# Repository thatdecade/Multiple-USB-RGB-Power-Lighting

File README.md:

# Multiple USB RGB Power Lighting
The goal of this project is to set the color of two neopixel rings based on which USB cable is powered.  I plugged the USB cables into my game consoles, so when a console is powered, the shelf llght will have the corresponding color.

**How it Works**

Plug each USB cable into your separate devices.  The isolation diodes allow the trinket to be powered by any or all of the USB cables.  Periodically, the trinket will read the input pins to determine which USB cable is powered and will play the programmed animation and colors or combination of colors.

The trinket needs pull down resistors to set the idle state of an input pin when a USB cable is not powered or left unattached.

----

**Part List**

* Trinket 5V - <https://amzn.to/3gpQX6z>
* NeoPixel Ring - 16 RGB - <https://amzn.to/34wuUcn>
* Wired Under Cabinet Puck Lights - <https://amzn.to/2YssTdl>
* Backpack PCB - <https://oshpark.com/shared_projects/CATpwF4r>
* Three diodes - <https://octopart.com/search?q=CMF04%28TE12L%2CQ%2CM%29>
* Three 10k resistors - <https://octopart.com/search?q=RC0603FR-0710KL>
* Three USB Cables (dollar store)

The backpack pcb is optional.  You can just as easily wire up the diodes and resistors on a protoboard.  

**Pin Assignments**

Not all pins on the Trinket are equal.  Be sure to read Adafruit's help pages <https://learn.adafruit.com/introducing-trinket/pinouts>  Pins 3 and 4 should not be used as inputs and will conflict with talking to a PC for programming.

* GPIO #0 - Red Input, Attach to +5V wire from the first USB cable
* GPIO #1 - Blue Input, Attach to +5V wire from the second USB cable
* GPIO #2 - Green Input, Attach to +5V wire from the third USB cable
* GPIO #3 - Neopixel Data
* GPIO #4 - Potentiometer (optional)

I added a quick disconnect to Pin 4 so when I wanted to connect to the PC, I could remove the potentiometer without soldering.

**Assembly**

If you have access to a 3d printer, an enclosure stl is provided.  Thread the cables through the enclosure sides before soldering.

Solder the resistors and diodes to the backpack, then wire into the trinket.  Strip the USB cables and identify the 5V and Ground wires.  Use a multimeter to be sure, but the 5V and Ground wires can also be identified by thickness.  The power wires should be thicker than the data wires.

*There is a RGB LED and three 220 ohm resistors on the backback pcb for debugging, leave them unpopulated.*

Take apart the puck light and remove the PCB.  Recycling the wiring that came with the puck light to wire into your neopixel rings.  Use hot glue or epoxy to add the neopixel ring behind the puck light's diffuser.

**Programming**

Use the arduino ide and adafruit neopixel library and adafruit trinket board package.  Be sure to read Adafruit's help pages for each module.

* <https://learn.adafruit.com/adafruit-arduino-ide-setup/arduino-1-dot-6-x-ide>
* <https://learn.adafruit.com/introducing-trinket/setting-up-with-arduino-ide>
* <https://github.com/adafruit/Adafruit_NeoPixel>

If you followed my pin assignments, you can use the code without modification.  After you get the neopixels to light up and changing based on which USB cable is powered.   You can explore modifying the colors and animations.

**Usage, Testing, and Setting Colors**

After initial programming, when you plug in each of the three USB cables you should see the ring light up red or blue or green.  Combinations are allowed.

If you installed the optional potentiometer, you can change the color selected by a USB cable without reprogramming using a PC.  There are 16 colors preprogrammed to select from.

1. You will need two USB power ports to plug into.  
2. Connect the Micro USB on the trinket so power remains on while the other USBs are unplugged.  Leave this plugged in throughout these steps.
3. Take the USB cable you want to configure and plug it into your power block.  
4. Wait 5 seconds (or just wait for the animation to complete)
5. Rapidly unplug and plug the cable in four times, ending with the USB plugged in.
    1. You must complete this four times, before the spinning animation ends.
    2. If you do it right, the animations will stop and you will see a steady light.  
    3. If you mess up, wait 5 seconds before trying again.
6. Slowly rotate the potentiometer to select the color.
7. Unplug the USB cable to save the color selection.

----

**Additional Notes**

I used the NeoPixel ring and Trinket I listed above because that is what I had extra.  If I were to make one from scratch, I would use the [RGBW Neopixel Rings](https://octopart.com/search?q=adafruit+2854) and [Arduino NANO 33 IoT](https://amzn.to/3lg6Tfj) instead.  So I could use the Puck Light for normal lighting with commands to Alexa to change colors too!  

More Info: <https://blog.arduino.cc/2019/11/12/create-a-voice-controlled-device-with-alexa-and-arduino-iot-cloud-in-7-minutes/>

_We are a participant in the Amazon Services LLC Associates Program, an affiliate advertising program designed to provide a means for us to earn fees by linking to Amazon.com and affiliated sites._

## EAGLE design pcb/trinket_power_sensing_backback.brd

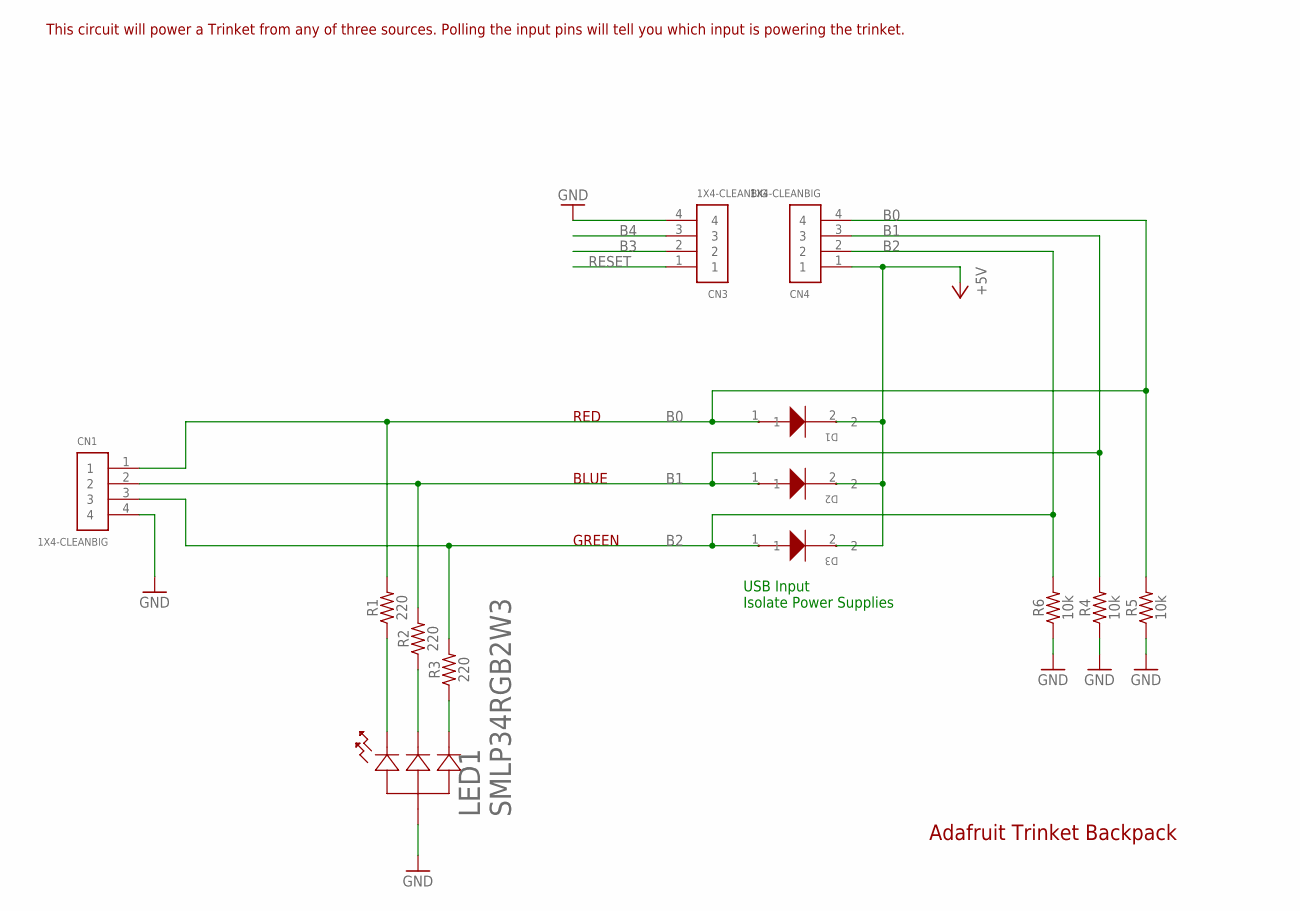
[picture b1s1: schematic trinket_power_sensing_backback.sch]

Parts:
CN1, CN3, CN4: 1X4-CLEANBIG; 1X04-CLEANBIG
D1, D2, D3: CMF04(TE12L,Q,M); M-FLAT_TOS
LED1: SMLP34RGB2W3; LED_SML-P24M_ROM
R1, R2, R3: 220; 0603
R4, R5, R6: 10k; 0603

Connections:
+5V: CN4.1, D1.2, D2.2, D3.2
B0: CN1.1, CN4.4, D1.1, R1.2, R5.2
B1: CN1.2, CN4.3, D2.1, R2.2, R4.2
B2: CN1.3, CN4.2, D3.1, R3.2, R6.2
B3: CN3.2
B4: CN3.3
GND: CN1.4, CN3.4, LED1.1, R4.1, R5.1, R6.1
unnamed: LED1.2, R1.1
unnamed: LED1.3, R2.1
unnamed: LED1.4, R3.1
RESET: CN3.1

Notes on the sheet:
Adafruit Trinket Backpack
USB Input Isolate Power Supplies
RED
BLUE
GREEN
This circuit will power a Trinket from any of three sources. Polling the input pins will tell you which input is powering the trinket.

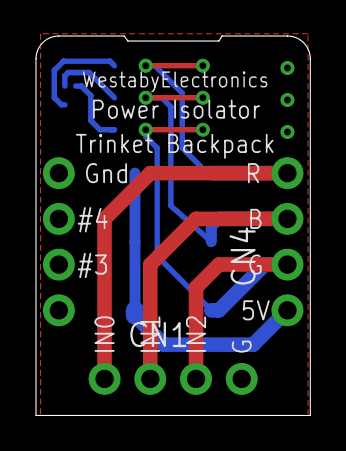
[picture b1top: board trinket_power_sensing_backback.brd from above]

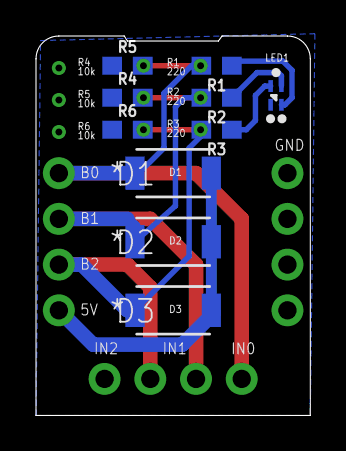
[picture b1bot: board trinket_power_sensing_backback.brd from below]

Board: 2 copper layers, 15.2 x 21.1 mm, 13 parts (10 on the bottom side), 8 nets.

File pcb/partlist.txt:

Partlist

EAGLE Version 7.7.0 Copyright (c) 1988-2016 CadSoft

Assembly variant: 

Part     Value            Package          Library            Position (inch)       Orientation

D1       CMF04(TE12L,Q,M) M-FLAT_TOS       CMF04(TE12L,Q)     (0.3 0.55)            MR0
D2       CMF04(TE12L,Q,M) M-FLAT_TOS       CMF04(TE12L,Q)     (0.3 0.4)             MR0
D3       CMF04(TE12L,Q,M) M-FLAT_TOS       CMF04(TE12L,Q)     (0.3 0.25)            MR0
LED1     SMLP34RGB2W3     LED_SML-P24M_ROM SMLP34RGB2W3A      (0.075 0.72)          MR90
R1       220              0603             SparkFun-Resistors (0.205 0.785)         MR180
R2       220              0603             SparkFun-Resistors (0.205 0.715)         MR180
R3       220              0603             SparkFun-Resistors (0.205 0.645)         MR180
R4       10k              0603             SparkFun-Resistors (0.4 0.715)           MR0
R5       10k              0603             SparkFun-Resistors (0.4 0.785)           MR0
R6       10k              0603             SparkFun-Resistors (0.4 0.645)           MR0

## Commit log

2020-08-25 Debugged
2020-08-25 3d enclosure
2020-08-25 Part photos
2020-08-25 photos of install
2020-08-26 Removed delays
2020-08-26 Colors are stored to EEPROM
2020-08-26 Colors are re-programmable without a PC
2020-08-26 Some debugging of color selections and setup entry
2020-08-26 Fixed bug in fade down animation
2020-08-26 Assembly photos

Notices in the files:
parts and their libraries:
SparkFun-Resistors: Licensing: Creative Commons ShareAlike 4.0 International - https://creativecommons.org/licenses/by-sa/4.0
COPYRIGHT: Copyright (C) 2018 Accelerated Designs. All rights reserved
